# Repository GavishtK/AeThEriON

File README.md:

<h1 align="center">AETHERION AI</h1>

<p align="center">
  <b>ESP32-Based Attitude Indicator &amp; Wireless Flight Instrumentation System</b>
  <br/>

</p>

<p align="center">
  <b>Real-time flight attitude indicator with a wireless OLED display and a full web-based analytics dashboard.</b>
</p>
<p align="center">
  <b>50 Hz telemetry | 25 FPS OLED | 60 FPS horizon | AI analysis | Flight recording &amp; replay | SQLite-quality sensor diagnostics</b>
</p>

---

## Table of Contents

1. [Project Overview](#overview)
2. [System Architecture](#system-architecture)
3. [Data Flow](#data-flow)
4. [Telemetry Protocol](#telemetry-protocol)
5. [Firmware](#firmware)
6. [Dashboard](#dashboard)
7. [Screenshots](#screenshots)
8. [PCB Design](#pcb-design)
9. [Hardware](#hardware)
10. [Quick Start](#quick-start)
11. [Development](#development)
12. [UI Testing](#ui-testing)
13. [License](#license)

---

## Overview 

AETHERION AI is a self-contained, open-source flight instrumentation system built on the ESP32. It combines:

- **Onboard OLED primary flight display (PFD)** — 128×64 monochrome display rendered at 25 FPS
- **Wireless web dashboard** — served directly from the ESP32 over Wi-Fi, accessed via any browser
- **Real-time attitude indicator** — artificial horizon with pitch ladder, roll arc, aircraft symbol, and turn coordinator
- **Flight telemetry** — 50 Hz broadcast of raw IMU data, computed attitude, and G-force over WebSocket
- **Flight recording & replay** — client-side session storage (IndexedDB), CSV/JSON export, and seekable playback
- **AI-powered analysis** — multi-model flight state classification (Random Forest, XGBoost, Neural Network, SVM)
- **Stability & control scoring** — RMS deviation, oscillation analysis, correction rate, and pilot stability metrics
- **Sensor health diagnostics** — saturation, noise, packet-loss, and data-quality analysis

The ESP32 runs in **Access Point mode**, creating its own Wi-Fi network so no router is required. The dashboard is stored on-board in LittleFS flash and served over HTTP, while telemetry is streamed over a WebSocket server at 50 Hz.

---

## System Architecture 

### Firmware Module Architecture

```mermaid
graph LR
    subgraph "firmware/Aetherion"
        A[Aetherion.ino<br/>Main Entry]
        B[config.h<br/>Configuration]
        C[imu.cpp/h<br/>Sensor Driver<br/>MPU6050 + Madgwick]
        D[graphics.cpp/h<br/>OLED Rendering<br/>U8g2 / PFD]
        E[web.cpp/h<br/>HTTP + WS Server<br/>LittleFS]
        F[rgb.cpp/h<br/>LED Status]
    end

    A --> B
    A --> C
    A --> D
    A --> E
    A --> F
    C -->|IMUData| D
    C -->|IMUData| A
    D -->|drawPFD| A
    E -->|handleWebClient| A
    F -->|Status| A
```

### Architecture Diagram (Image)

---

## Data Flow 

```mermaid
sequenceDiagram
    participant ESP32 as ESP32
    participant IMU as MPU6050 (I2C)
    participant OLED as OLED Display
    participant Browser as Web Browser
    participant IndexedDB as IndexedDB (Local)

    loop Setup (one-time)
        ESP32->>IMU: Initialize (I2C 0x68)
        ESP32->>IMU: Calibrate (200 samples)
        ESP32->>OLED: Boot Screen → Loading → Ready
        ESP32->>ESP32: Create I2C Mutex
        ESP32->>ESP32: Create oledTask (FreeRTOS, 25 FPS)
        ESP32->>WiFi: softAP("Aetherion", "aetherion123")
        ESP32->>WS: WebSocket Server begin (port 81)
        ESP32->>HTTP: LittleFS mount + WebServer begin (port 80)
    end

    par oledTask (25 FPS, Core 0)
        loop every 40 ms
            oledTask->>IMU: xSemaphoreTake(i2cMutex)
            IMU->>oledTask: Read accel + gyro
            oledTask->>oledTask: Compute roll/pitch (atan2)
            oledTask->>OLED: drawPFD(roll, pitch, gForce)
            oledTask->>oledTask: xSemaphoreGive(i2cMutex)
        end
    end

    par Main Loop (50 Hz)
        loop every 20 ms
            ESP32->>Web: handleWebClient() (HTTP)
            ESP32->>WS: webSocket.loop() (WebSocket)
            ESP32->>IMU: xSemaphoreTake(i2cMutex, 5 ms)
            IMU->>ESP32: updateIMU() — raw accel, gyro, computed attitude
            ESP32->>ESP32: xSemaphoreGive(i2cMutex)
            ESP32->>Browser: WebSocket broadcastTXT(JSON) at 50 Hz
        end
    end

    Note over Browser,DB: Browser receives 50 Hz telemetry
    Browser->>Browser: Parse JSON packet
    Browser->>Browser: Update horizon (60 FPS via requestAnimationFrame)
    Browser->>Browser: Update telemetry readouts (15 Hz)
    Browser->>Browser: Update live graphs (15 FPS)
    Browser->>Browser: Detect flight state (10 Hz rule-based)
    Browser->>IndexedDB: Store snapshot on record
```

### Telemetry Packet Format

Every 20 ms (50 Hz), the ESP32 broadcasts a JSON packet:

```json
{
  "t": 1543210,
  "roll": -4.23,
  "pitch": 2.15,
  "gForce": 1.02,
  "ax": 0.123,
  "ay": -0.045,
  "az": 9.782,
  "gx": 0.001,
  "gy": -0.003,
  "gz": 0.002
}
```

| Field     | Type   | Unit     | Description                          |
|-----------|--------|----------|--------------------------------------|
| `t`       | uint32 | ms       | ESP32 uptime (for clock sync)        |
| `roll`    | float  | degrees  | Roll angle (-180° to +180°)          |
| `pitch`   | float  | degrees  | Pitch angle (-90° to +90°)           |
| `gForce`  | float  | G        | Resultant G-force (1.0 = level)      |
| `ax/ay/az`| float  | m/s²     | Accelerometer raw values             |
| `gx/gy/gz`| float  | rad/s    | Gyroscope raw values                 |

---

## Firmware 

The ESP32 firmware is an Arduino sketch (`Aetherion.ino`) with modular C++ components.

### File Structure

```
firmware/Aetherion/
├── Aetherion.ino      # Main entry point: setup() + loop()
├── config.h           # Pin assignments, WiFi creds, constants
├── imu.cpp            # MPU6050 driver + sensor fusion
├── imu.h              # IMU data structure + API
├── graphics.cpp       # OLED rendering (PFD, boot screen, loading)
├── graphics.h         # Graphics API declarations
├── web.cpp            # HTTP + WebSocket server (LittleFS)
├── web.h              # Web server API declarations
├── rgb.cpp            # RGB LED status indicator
├── rgb.h              # RGB LED API declarations
├── sync_dashboard.ps1 # Syncs dashboard files to LittleFS data/
└── data/              # Dashboard served from LittleFS
    ├── index.html
    ├── style.css
    └── js/
        ├── app.js           # Core app: WebSocket, render loop
        ├── horizon.js        # Canvas artificial horizon
        ├── graphs.js         # Live telemetry graphs
        ├── flight-state.js   # Rule-based state detection
        ├── recorder.js       # Flight recording + IndexedDB
        ├── analysis.js       # Replay, stability, ML panels
        └── settings.js       # Persistent settings (localStorage)
```

### Key Features

| Feature             | Details                                                                 |
|---------------------|-------------------------------------------------------------------------|
| **IMU Sensing**     | MPU6050 accelerometer + gyroscope via I2C (400 kHz)                   |
| **Attitude Calc.**  | Roll/Pitch via `atan2` with 200-sample static calibration offset         |
| **G-Force**         | Resultant acceleration vector magnitude normalized to G                 |
| **OLED Display**    | 128×64 SH1106, drawn at 25 FPS via dedicated FreeRTOS task               |
| **PFD Elements**    | Pitch ladder, roll arc with tick marks, aircraft symbol, turn coord.  |
| **WiFi**            | ESP32 in AP mode — SSID `Aetherion`, password `aetherion123`            |
| **WebSocket**       | Broadcasts JSON telemetry at 50 Hz (port 81)                          |
| **HTTP Server**     | Serves dashboard from LittleFS (port 80)                                |
| **FreeRTOS**        | `oledTask` on Core 0 at priority 1 with I2C mutex                       |
| **RGB LED**         | Red (boot) → Purple (init) → Blue (connecting) → Green (ready)          |
| **I2C Mutex**       | Serializes access between main loop (IMU read) and oledTask (OLED draw) |

### Boot Sequence

```mermaid
flowchart TD
    A[Power On] --> B[Serial Init 115200]
    B --> C[initDisplay + initRGB]
    C --> D[RGB Red: Boot Screen]
    D --> E[Delay 1500ms]
    E --> F[RGB Purple: Initializing]
    F --> G[initIMU]
    G --> H[calibrateIMU 200 samples]
    H --> I[Wire.setClock 400kHz]
    I --> J[WiFi.softAP]
    J --> K[WebSocket Server on :81]
    K --> L[initFileSystem + initWebServer]
    L --> M[RGB Purple: Loading Screen 0-96]
    M --> N[RGB Blue: Ready Screen]
    N --> O[Delay 1000ms]
    O --> P[RGB Green: Ready]
    P --> Q[Create I2C Mutex]
    Q --> R[Create oledTask FreeRTOS]
    R --> S[Main Loop: 50 Hz]
```

---

## Dashboard 

The web dashboard is a single-page application (SPA) written in vanilla JavaScript with no external framework dependencies. It uses HTML5 Canvas for all rendering and IndexedDB for local session storage.

### Architecture

```mermaid
graph TB
    subgraph "Dashboard Modules"
        App[app.js<br/>Core Engine<br/>WebSocket, Render Loop]
        Horizon[horizon.js<br/>Artificial Horizon<br/>Canvas 2D]
        Graphs[graphs.js<br/>Live Telemetry Graphs<br/>Canvas 2D]
        FlightState[flight-state.js<br/>State Detection<br/>Rule-based]
        Recorder[recorder.js<br/>Flight Recorder<br/>IndexedDB]
        Analysis[analysis.js<br/>Replay + AI Analysis]
        Settings[settings.js<br/>Config + localStorage]
        Style[style.css<br/>Dark Theme UI]
    end

    App --> Horizon
    App --> Graphs
    App --> FlightState
    App --> Recorder
    App --> Analysis
    App --> Settings
    App --> Style
    App -->|WebSocket| ESP32[ESP32 Telemetry]
    Horizon -->|registerCallback horizon| App
    Graphs -->|registerCallback graph| App
    FlightState -->|registerCallback state| App
    Recorder -->|registerCallback packet+graph| App
    Analysis -->|loadSession| Recorder
    Settings -->|load/save| App
```

### Render Loop Architecture

The dashboard uses a **throttled multi-rate render loop** driven by `requestAnimationFrame`:

| Component           | Rate   | Trigger            | Description                          |
|---------------------|--------|--------------------|--------------------------------------|
| Artificial Horizon  | 60 FPS | `requestAnimationFrame` | Canvas redraw, smooth attitude    |
| Telemetry Readouts  | 15 Hz  | Time-based throttle | Text updates for accel/gyro/attitude|
| Live Graphs         | 15 FPS | Time-based throttle | Canvas graph plots (roll/pitch/G/gyro)|
| Flight State        | 10 Hz  | Time-based throttle | Rule-based state detection          |
| Diagnostics         | 2 Hz   | Time-based throttle | Packet count, FPS, latency, uptime  |
| Packet Callbacks    | 50 Hz  | On every packet     | Recording data capture              |

### Tab Navigation

The dashboard has four tabs:

1. **LIVE** — Real-time attitude indicator, telemetry panel, live graphs, flight state, and status bar
2. **RECORD** — Flight recording controls, session management, recording preview graph
3. **ANALYSIS** — Flight replay, stability metrics, control analysis, sensor health, system performance, AI analysis panel
4. **SETTINGS** — Connection configuration, telemetry settings, display options

### Flight States

The rule-based flight state detector identifies these states:

| State          | Color   | Trigger Condition                                  |
|----------------|---------|----------------------------------------------------|
| LEVEL          | Green   | Roll < 30°, pitch < 8°, G within 0.5–1.8           |
| TURNING LEFT   | Cyan    | Roll < -30°                                         |
| TURNING RIGHT  | Cyan    | Roll > +30°                                         |
| CLIMBING       | Amber   | Pitch > 15°                                         |
| DESCENDING     | Amber   | Pitch < -15°                                        |
| PITCH-UP       | Orange  | Pitch > 8°                                          |
| PITCH-DOWN     | Orange  | Pitch < -8°                                         |
| ROLLING        | Magenta | |gx|, |gy| > 0.15 or |gz| > 0.1                 |
| RECOVERING     | Cyan    | Roll < 15° and trending toward level               |
| UNSTABLE       | Red     | G-force > 1.8 or < 0.5                              |

### AI Analysis Models

The Analysis tab supports four ML models for flight state classification:

| Model            | Use Case                              | Accuracy Estimate |
|------------------|---------------------------------------|-------------------|
| Random Forest    | Fast, robust baseline classification  | ~92%              |
| XGBoost          | Gradient boosting, handles edge cases | ~94%              |
| Neural Network   | Deep pattern recognition              | ~90%              |
| SVM              | Linear separability, low compute      | ~88%              |

### Stability Metrics

| Metric              | Description                                                   |
|---------------------|---------------------------------------------------------------|
| Roll RMS            | Root-mean-square roll deviation                               |
| Pitch RMS           | Root-mean-square pitch deviation                              |
| Angular-rate RMS    | RMS of combined gyroscope rates (gx+gy+gz)                    |
| Roll Peak           | Maximum absolute roll                                         |
| Pitch Peak          | Maximum absolute pitch                                        |
| G-Force Peak        | Maximum G-force recorded                                      |
| Stability Score     | Composite 0-100 score: 100 - weighted deviation penalties     |
| Data Quality        | Sensor health score factoring missing packets, saturation, noise |

### Control Analysis

| Metric              | Description                                                   |
|---------------------|---------------------------------------------------------------|
| Roll Control        | RMS-based quality rating (Good/Moderate/Fair/Poor)            |
| Pitch Control       | RMS-based quality rating                                      |
| Correction Rate     | Frequency of roll direction changes per second                |
| Oscillation         | Std dev of roll deltas (control stability)                    |
| Recovery            | RMS of roll in final 20% of flight (settling quality)         |

---

## Screenshots 

### Dashboard — Live Tab

Real-time attitude indicator with artificial horizon, telemetry panel, live graphs, flight state, and status bar:

### Dashboard — Record Tab

Flight recording controls, session list, and recording preview graph:

### Dashboard — Analysis Tab

Flight replay, stability metrics, control analysis, sensor health, system performance, and AI analysis:

### Dashboard — Settings Tab

Connection settings (ESP32 IP, WebSocket port), telemetry configuration, and display options:

### UI Test Screenshots

Automated Playwright test captures of all dashboard states:

**Full Dashboard** — Initial render of the complete dashboard:

**Panel Hover** — 3D perspective transform on panel hover:

**Record Tab** — Recording interface with session list:

**Analysis Tab** — Flight replay and analysis panels:

**Settings Tab** — Configuration panels:

**Live Tab (returned)** — Back to live attitude display:

---

## PCB Design 

KiCad project files for the Aetherion hardware. The PCB integrates all components on a single 2-layer board.

### PCB View Gallery

**Schematic** — Complete circuit schematic:

**PCB Layout (Routed)** — Top-layer copper routing:

**3D Render** — Isometric 3D view of the assembled PCB:

**Circuit Diagram (Concept)** — Conceptual circuit overview:

### PCB File Structure

```
pcb/
├── schematic/           # KiCad schematic files (.kicad_sch)
├── pcb-layout/          # KiCad PCB layout files (.kicad_pcb, .kicad_pro)
├── library/
│   ├── SSD1306-128x64_OLED.kicad_sym           # OLED symbol
│   ├── SSD1306.pretty/
│   │   └── 128x64OLED.kicad_mod               # OLED footprint
│   └── AeroGyro.pretty/
│       └── LED_D5.0mm-4_RGB_AeroGyro.kicad_mod.pretty/
│           └── LED_D5.0mm-4_RGB.kicad_mod     # RGB LED footprint
└── manufacturing/       # Gerber and drill files (for fabrication)
```

### Design Features

| Feature             | Details                                                             |
|---------------------|---------------------------------------------------------------------|
| Form Factor         | ESP32 DevKit compatible                                              |
| IMU Connector       | 4-pin I2C header (SDA, SCL, VCC, GND) for MPU6050                    |
| OLED Connector      | I2C header (4-pin: SDA, SCL, VCC, GND) for 0.96" SSD1306 display    |
| RGB LED             | Common cathode, 3-pin current-limited output                         |
| I2C Pull-ups        | 4.7kΩ resistors on SDA and SCL                                      |
| Power               | USB-C input with onboard 3.3V regulator                                |
| Dimensions          | Compact handheld form factor                                         |

---

## Hardware 

### Components

| Component        | Specification                                           |
|------------------|---------------------------------------------------------|
| **MCU**          | ESP32 DevKit (dual-core, 240 MHz, 520 KB RAM)           |
| **IMU**          | MPU6050 (3-axis accelerometer + 3-axis gyroscope)        |
| **Display**      | 0.96" OLED, 128×64 pixels, SSD1306/SH1106, I2C (0x3C)    |
| **RGB LED**      | Common Cathode, 3-pin (Red: GPIO19, Green: GPIO18, Blue: GPIO17) |
| **WiFi**         | 802.11 b/g/n, Access Point mode                          |
| **I2C Bus**      | SDA: GPIO21, SCL: GPIO22, Clock: 400 kHz                 |
| **WebSocket**    | Port 81 — telemetry broadcast                            |
| **HTTP Server**  | Port 80 — dashboard serving via LittleFS                 |

---

## Quick Start 

### Prerequisites

- Arduino IDE 2.0+ (or PlatformIO)
- ESP32 board package (`https://raw.githubusercontent.com/espressif/arduino-esp32/gh-pages/package_esp32_index.json`)
- Libraries: `Adafruit MPU6050`, `Adafruit Unified Sensor`, `U8g2`, `ESP Async WebServer`, `LittleFS`, `WebSockets`, `WebServer`

### Setup Steps

1. **Install ESP32 board support** in Arduino IDE:
   - File → Preferences → Additional Boards Manager URLs
   - Add: `https://raw.githubusercontent.com/espressif/arduino-esp32/gh-pages/package_esp32_index.json`
   - Tools → Board → Boards Manager → Install `esp32`

2. **Install required libraries** via Library Manager:
   ```
   Adafruit MPU6050
   Adafruit Unified Sensor
   U8g2 (by olikraus)
   LittleFS_esp32
   WebSockets
   ```

3. **Open the firmware**:
   ```
   firmware/Aetherion/Aetherion.ino
   ```

4. **Upload to ESP32** via Arduino IDE.

5. **Connect to Wi-Fi**:
   - Network: `Aetherion`
   - Password: `aetherion123`

6. **Open the dashboard**:
   - Navigate to `http://192.168.4.1` in any browser

### Syncing Dashboard Updates

When dashboard files are updated during development, sync them to the firmware's LittleFS data folder before uploading:

```powershell
# From the firmware directory
.\Aetherion\sync_dashboard.ps1
```

Then upload via Arduino IDE: `Tools → ESP32 Sketch Data Upload`

---

## Development 

### Project Structure

```
Aetherion/
├── firmware/                    # ESP32 Arduino firmware
│   └── Aetherion/
│       ├── Aetherion.ino        # Main sketch
│       ├── config.h             # Configuration
│       ├── imu.cpp / imu.h      # IMU sensor driver
│       ├── graphics.cpp / graphics.h  # OLED rendering
│       ├── web.cpp / web.h      # HTTP/WebSocket server
│       ├── rgb.cpp / rgb.h      # RGB LED control
│       ├── sync_dashboard.ps1   # Dashboard sync script
│       └── data/                # Dashboard files (LittleFS)
├── dashboard/                   # Standalone web dashboard (dev)
│   ├── index.html
│   ├── style.css
│   └── js/
│       ├── app.js               # Core application
│       ├── horizon.js           # Artificial horizon
│       ├── graphs.js            # Flight graphs
│       ├── flight-state.js      # Flight state detection
│       ├── recorder.js          # Flight recording
│       ├── analysis.js          # AI analysis
│       └── settings.js          # Configuration
├── aetherion-ui-test/           # Playwright UI tests
│   ├── index.html               # Test UI (with GSAP + 3D animations)
│   ├── test-ui.js               # Automated screenshot tests
│   ├── style.css
│   ├── js/
│   │   ├── app.js               # Enhanced: GSAP animations, pulse telemetry
│   │   ├── animations.js        # GSAP animation orchestration
│   │   ├── horizon.js           # Enhanced: 3D perspective transform
│   │   ├── graphs.js            # Enhanced: graph reveal animations
│   │   ├── recorder.js          # Recording + IndexedDB
│   │   ├── flight-state.js      # State detection
│   │   ├── analysis.js          # Analysis + ML panel
│   │   └── settings.js          # Settings
│   └── screenshots/             # Test screenshots
├── pcb/                         # KiCad PCB design files
│   ├── schematic/
│   ├── pcb-layout/
│   ├── library/
│   └── manufacturing/
├── screenshots/                 # Project screenshots & diagrams
├── memory/                      # Memory/knowledge base
├── LICENSE                      # MIT License
├── .gitignore
└── README.md                    # This file
```

### Firmware Development

The firmware follows a modular architecture:

1. **`Aetherion.ino`** — Orchestrates all modules in `setup()` and `loop()`. The main loop is intentionally lightweight: HTTP handling, WebSocket servicing, IMU reads (mutex-protected), and 50 Hz telemetry broadcast.
2. **`imu.cpp`** — MPU6050 driver using Adafruit library. Performs 200-sample calibration on boot, computes roll/pitch via `atan2`, and calculates resultant G-force.
3. **`graphics.cpp`** — U8g2-based OLED renderer. Draws a full PFD (Primary Flight Display) including pitch ladder, roll arc, aircraft symbol, battery indicator, and Wi-Fi icon.
4. **`web.cpp`** — Serves dashboard files from LittleFS over HTTP and broadcasts telemetry over WebSocket (port 81).
5. **`rgb.cpp`** — Simple RGB LED status indicator using direct GPIO control.

### Dashboard Development

The dashboard is a vanilla JavaScript SPA with no framework dependencies. Key architectural decisions:

- **Decoupled architecture**: WebSocket packet reception is completely separate from the render loop. Packets update a central `AG` state object; the render loop reads from it.
- **Throttled multi-rate rendering**: Different UI components update at different rates to balance performance and responsiveness.
- **No external dependencies** (in production firmware): The production dashboard uses zero external libraries. The `aetherion-ui-test/` variant adds GSAP for 3D animation testing.

---

## UI Testing 

The `aetherion-ui-test/` directory contains an enhanced version of the dashboard with GSAP-powered 3D animations, used for visual testing.

### Running Tests

```bash
cd aetherion-ui-test
npm install playwright
node test-ui.js
```

The test script uses Playwright to:

1. Load the dashboard HTML in a headless Chromium browser
2. Capture screenshots of the full dashboard and each tab
3. Test 3D panel hover effects
4. Verify JavaScript module loading (GSAP, Animations, Horizon, etc.)
5. Check for JavaScript errors
6. Validate CSS perspective transforms

### Test Screenshots

| # | Screenshot                  | Tab        | Description                              |
|---|-----------------------------|------------|------------------------------------------|
| 1 | `01-full-dashboard.png`     | Live       | Full dashboard initial render            |
| 2 | `02-panel-hover.png`        | Live       | 3D perspective on panel hover            |
| 3 | `03-record-tab.png`         | Record     | Recording interface                      |
| 4 | `04-analysis-tab.png`       | Analysis   | Flight replay + analysis panels          |
| 5 | `05-settings-tab.png`       | Settings   | Configuration panels                     |
| 6 | `06-live-tab-returned.png`  | Live       | Return to live attitude display          |

---

## License 

MIT License — see [LICENSE](LICENSE) for details.

Copyright (c) 2026 Aetherion

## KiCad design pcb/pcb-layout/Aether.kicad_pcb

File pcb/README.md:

# PCB Design

KiCad project files for the AeroGyro hardware.

## Structure

- `schematic/` - KiCad schematic files
- `pcb-layout/` - KiCad PCB layout files
- `footprints/` - Custom component footprints
- `symbols/` - Custom schematic symbols
- `manufacturing/` - Gerber and drill files for fabrication
- `3d/` - 3D model exports

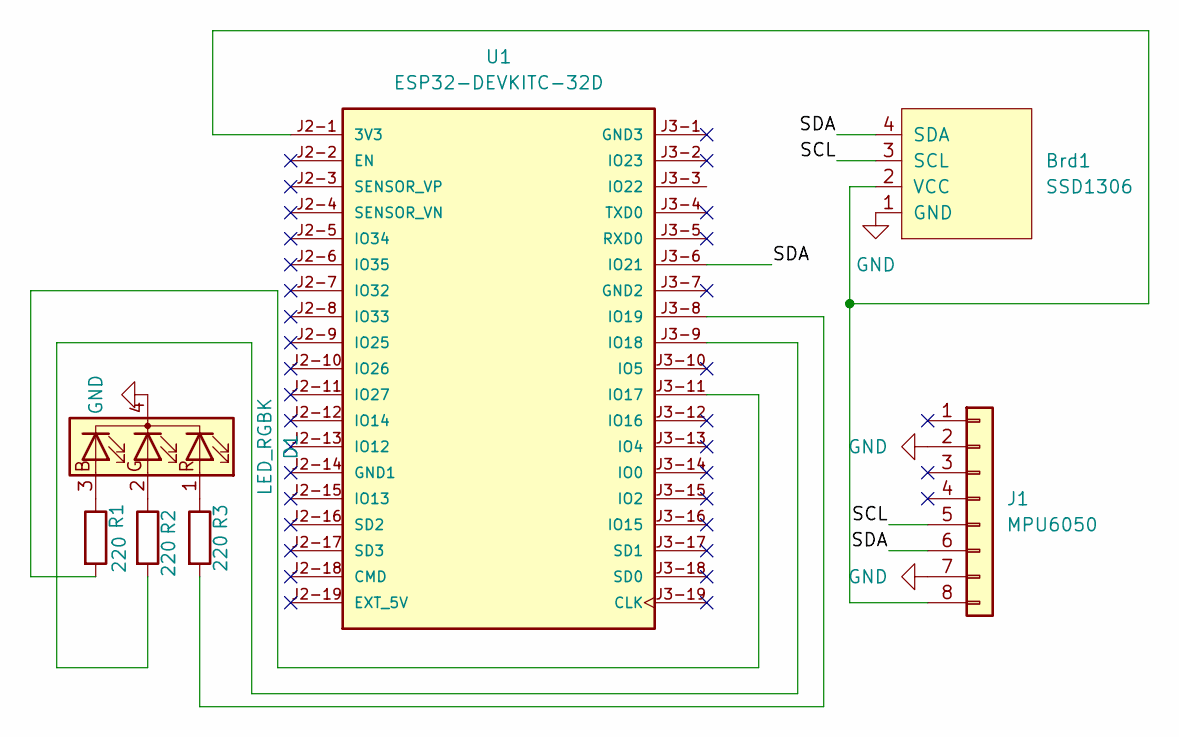
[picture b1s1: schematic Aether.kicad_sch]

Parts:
Brd1: SSD1306; 128x64OLED
D1: LED_RGBK; LED_D5.0mm-4_RGB
J1: MPU6050; PinHeader_1x08_P2.54mm_Vertical
R1, R2, R3: 220; R_Axial_DIN0207_L6.3mm_D2.5mm_P10.16mm_Horizontal
U1: ESP32-DEVKITC-32D; MODULE_ESP32-DEVKITC-32D; PARTREV V4

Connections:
/SCL: Brd1.3 (SCL), J1.5 (SCL)
/SDA: Brd1.4 (SDA), J1.6 (SDA), U1.J3-6 (IO21)
GND: Brd1.1 (GND), D1.4 (K), J1.2 (AD0), J1.7 (GND)
unnamed: Brd1.2 (VCC), J1.8 (VCC), U1.J2-1 (3V3)
unnamed: D1.3 (BA), R1.1
unnamed: D1.2 (GA), R2.1
unnamed: D1.1 (RA), R3.1
unnamed: R1.2, U1.J3-11 (IO17)
unnamed: R2.2, U1.J3-9 (IO18)
unnamed: R3.2, U1.J3-8 (IO19)

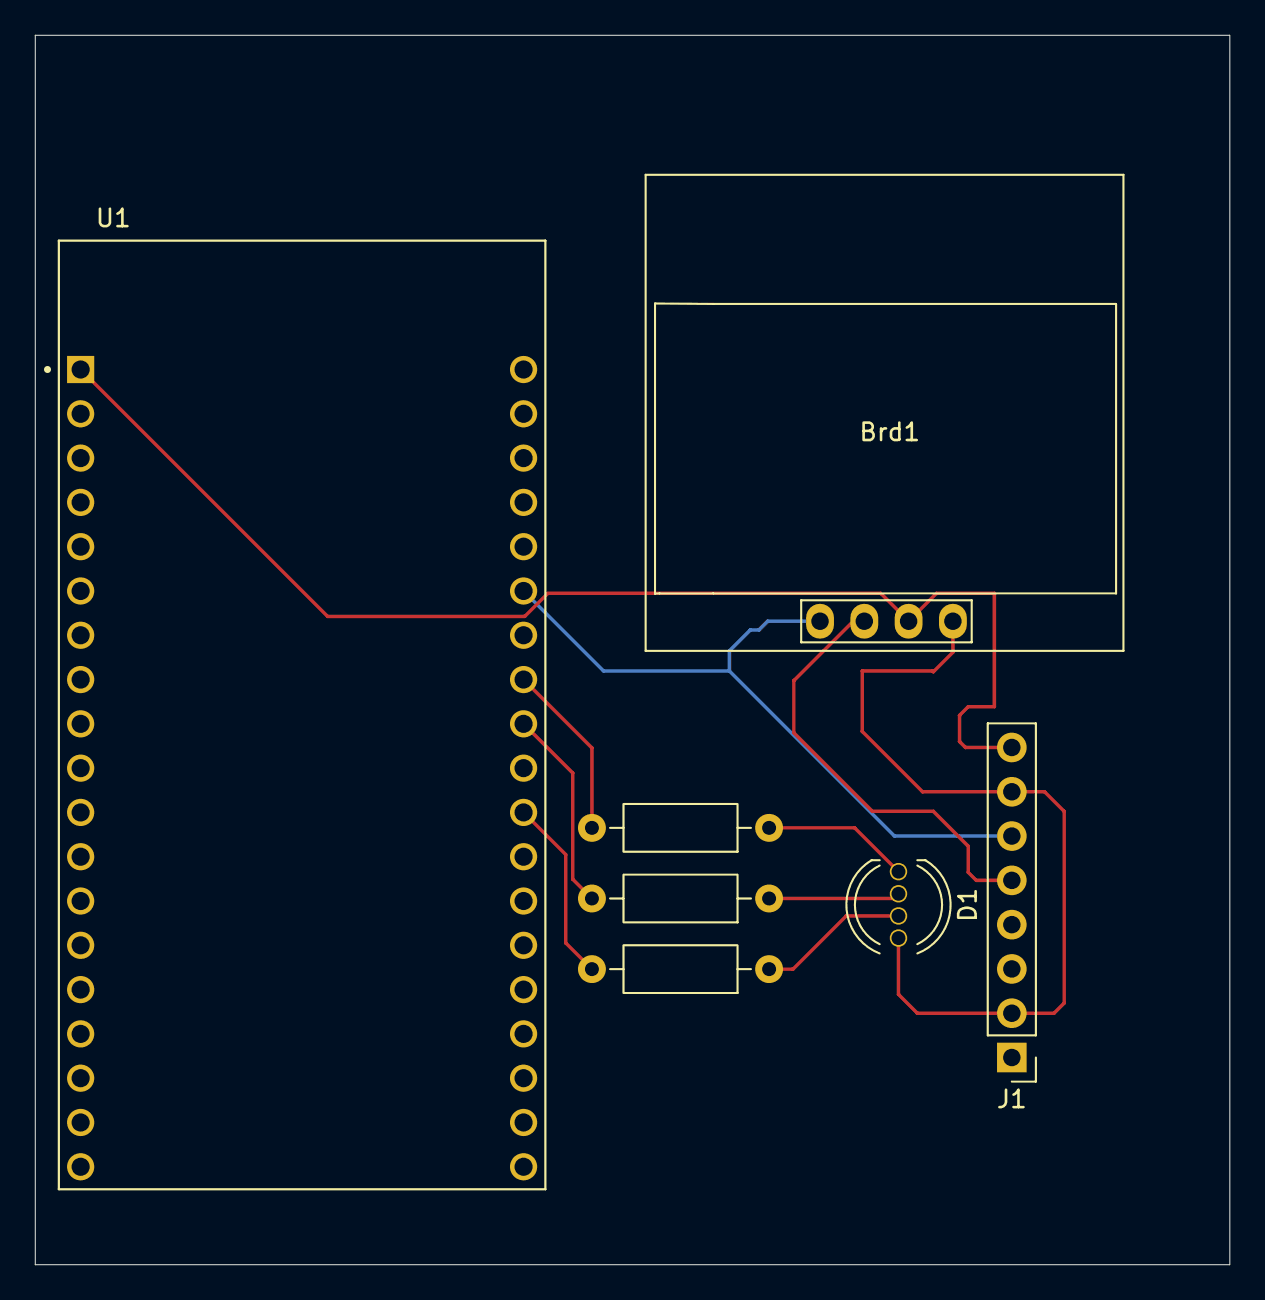
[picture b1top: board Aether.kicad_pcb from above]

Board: 2 copper layers, 68.5 x 70.5 mm, 7 parts (0 on the bottom side), 10 nets.
